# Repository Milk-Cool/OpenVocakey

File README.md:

# OpenVocakey
An open-source ESP32-based vocal synthesis keyboard

## What is this?
This is exactly what it sounds like -- a DIY open-source keyboard capable of producing human-like speech in the form of singing. Yes, just like VOCALOID -- except it is live, so it would be closer to [Pocket Miku](https://youtu.be/Uk6hSK1DDR4) or the [VOCALOID Keytar](https://en.wikipedia.org/wiki/Vocaloid_Keyboard).

### What is this based on?
It uses [espeak-ng](https://github.com/espeak-ng/espeak-ng) at its core, with the wrapper being [BackgroundAudio](https://github.com/earlephilhower/BackgroundAudio) and the wrapper wrapper being `tts.cpp`. This means that the voices are actually very customizable! You can use formant settings to adjust the voice to your liking and then upload it to the device.

## How do I use it?
You can buy a [Cardputer](https://shop.m5stack.com/products/m5stack-cardputer-adv-version-esp32-s3) if you wanna check the project out, or make a keyboard of your own with the provided gerber and KiCad files. Then, you can upload songs and files using the [online tool](https://milk-cool.github.io/OpenVocakey/) (works best with Chromium-based browsers).

### Song format
A song is just a text file containing Japanese characters (hiragana or katakana but NOT kanji), with each syllable on its own line, for example:
```
き
ら
き
ら
ひ
か
る
```

You can also add ending syllables after a base syllable, separated by a comma (will not be stretched):
```
こ,い
```

> Note: you can input more than one syllable on one line, but then the vowel stretch won't work properly.

### Voice format
This is just an espeak-ng voice, but without the `pitch` and `language` fields (those are added automatically). See [the documentation for espeak-ng](https://github.com/espeak-ng/espeak-ng/blob/master/docs/voices.md) for specific instructions on how to create a voice.

### Assembling the board
If you decided to make your own keyboard, first of all, you'd have to order a two-layer PCB. This is because one of the traces (yes, just one!) is on the other side of the PCB. Then, once it arrives, you have to solder MX-Cherry style keyboard switches into the holes on the bottom of the board (and add keycaps to your liking) and solder on female 2.54mm headers everywhere else. Then, you can insert a 30-pin ESP32-WROOM board into the double headers (with the USB port facing outwards), an i2c SSD1306 display into the middle headers (facing inwards) and a MAX98357a i2s audio amplifier into the remaining headers (facing outwards; don't forget to connect a speaker!!). Also don't forget to solder on the 10K resistors for pull-up below the ESP32. Then you can print out the case (`case/`), slide the board inside and screw it down on the sides with M6x20 bolts. Then you'd have to upload the firmware to the ESP32 and you're done!!

> Note: see `bom.csv` for the Bill of Materials.

### Navigating the menus
You can press BOOT/G0 on your board to enter the menu. From there, you can press the two leftmost white buttons to move left or right, and the rightmost two white buttons for cancelling and confirming your actions (e. g. entering a submenu and then confirming the volume change using the rightmost button). You can also press G0 again to leave the menu.

Go on, play around with the menus and see what you can customize!!

> Note: most settings are discarded upon reboot.

### Using the website

You can use the [online tool](https://milk-cool.github.io/OpenVocakey/) to manage the files on your OpenVocakey. First, click "Connect" in the corner and select your board. Then, you can download the already existing files by clicking on them, or upload new files by first selecting the file, then giving it a name and then clicking "upload".

> Note: that **WILL** overwrite the file! Be careful.

## Why does this exist?
I was always fascinated by vocaloids and the two aforementioned products in paticular, hence I decided to make this. Those can be hard to get and rather unaffordable, especially in non-first-world countries, therefore I think people might find this useful.

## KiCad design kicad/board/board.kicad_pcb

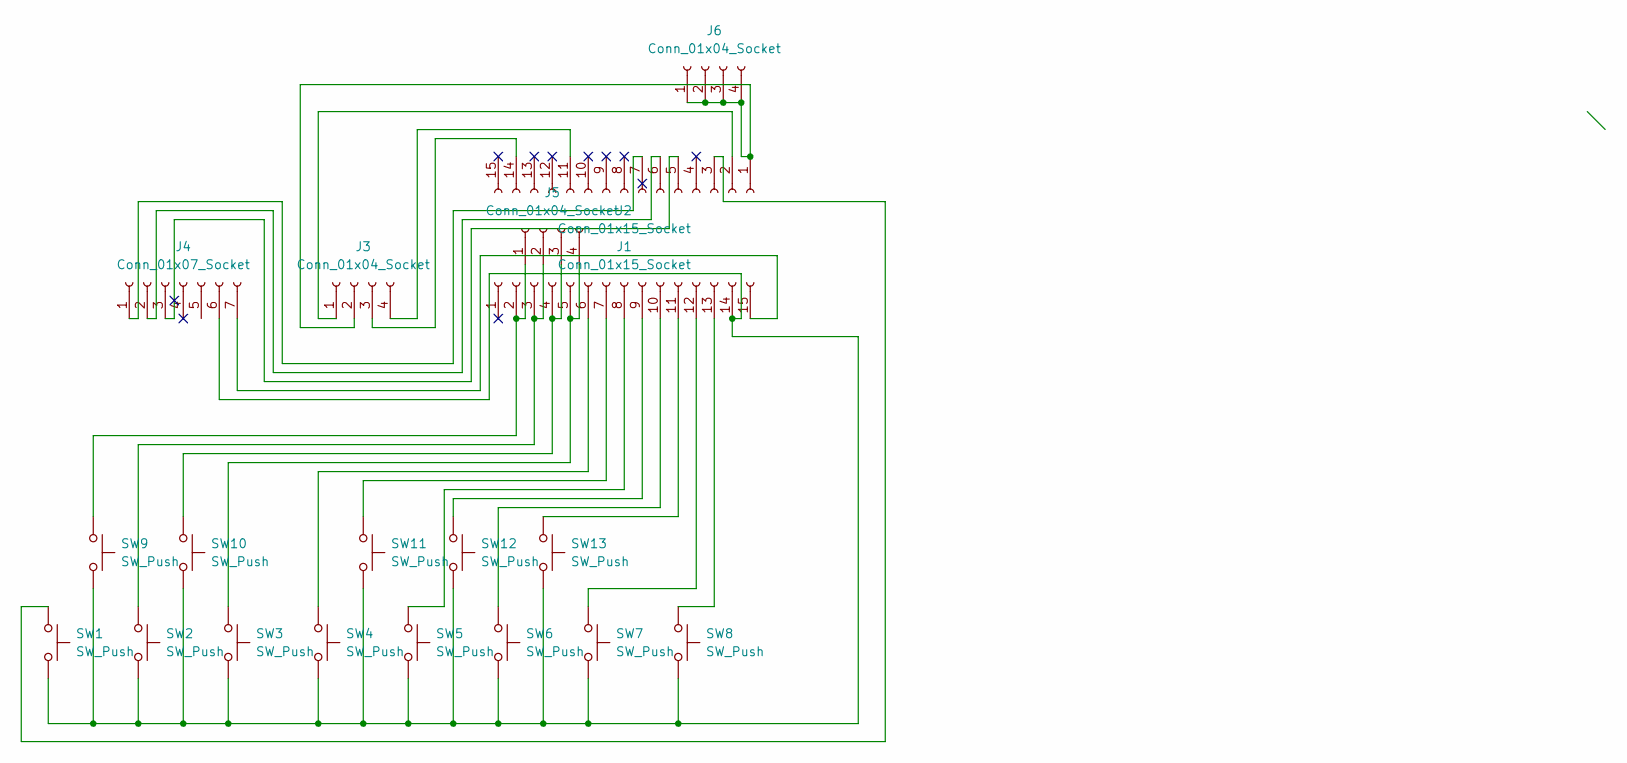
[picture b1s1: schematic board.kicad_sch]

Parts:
J1, J2: Conn_01x15_Socket; PinHeader_1x15_P2.54mm_Vertical
J3, J5, J6: Conn_01x04_Socket; PinHeader_1x04_P2.54mm_Vertical
J4: Conn_01x07_Socket; PinHeader_1x07_P2.54mm_Vertical
SW1, SW2, SW3, SW4, SW5, SW6, SW7, SW8, SW9, SW10, SW11, SW12, SW13: SW_Push; SW_Cherry_MX_1.00u_PCB

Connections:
unnamed: J1.2, J5.1, SW9.1
unnamed: J1.3, J5.2, SW2.1
unnamed: J1.4, J5.3, SW10.1
unnamed: J1.5, J5.4, SW3.1
unnamed: J1.6, SW4.1
unnamed: J1.7, SW11.1
unnamed: J1.8, SW5.1
unnamed: J1.9, SW12.1
unnamed: J1.10, SW6.1
unnamed: J1.11, SW13.1
unnamed: J1.12, SW7.1
unnamed: J1.13, SW8.1
unnamed: J1.14, J4.6, SW1.2, SW2.2, SW3.2, SW4.2, SW5.2, SW6.2, SW7.2, SW8.2, SW9.2, SW10.2, SW11.2, SW12.2, SW13.2
unnamed: J1.15, J4.7
unnamed: J2.1, J3.2, J6.1, J6.2, J6.3, J6.4
unnamed: J2.2, J3.1
unnamed: J2.3, SW1.1
unnamed: J2.5, J4.3
unnamed: J2.6, J4.2
unnamed: J2.7, J4.1
unnamed: J2.11, J3.4
unnamed: J2.14, J3.3

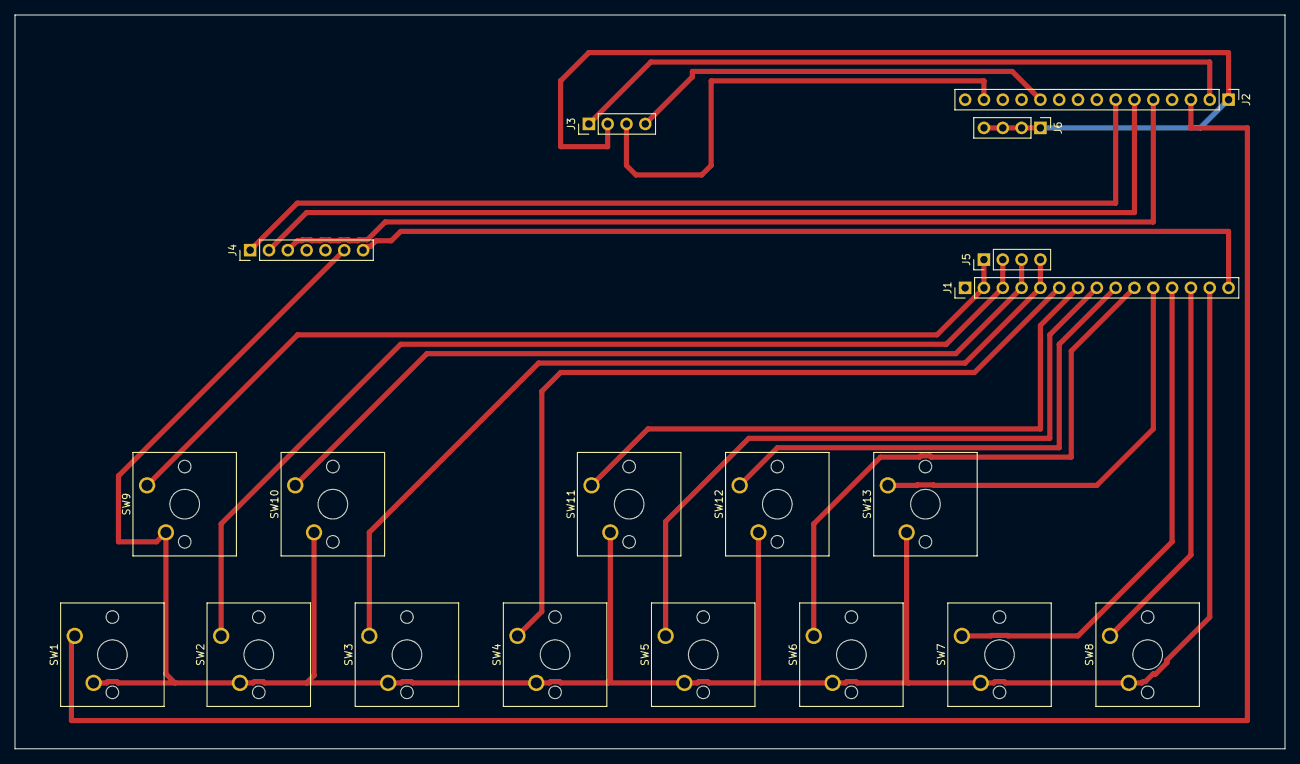
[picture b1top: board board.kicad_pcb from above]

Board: 2 copper layers, 171.4 x 99.1 mm, 19 parts (0 on the bottom side), 22 nets.

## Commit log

2026-04-30 YAAYA i figured out the pitch
2026-04-30 SOME SUCCESS!!!
2026-04-30 switch to japanese only
2026-04-30 twinkle twinkle little star played with the keyboard!!
2026-04-30 made it just a little faster
2026-05-01 a potential slight performance fix
2026-05-01 patch library to have a smaller audio buffer
2026-05-01 it's in tune now!
2026-05-01 added lyrics display
2026-05-01 songs and voicebanks storage
2026-05-01 prolong the vowels more
2026-05-02 reset button
2026-05-02 rewrite input stack
2026-05-02 add option to change wpm and vowel stretch
2026-05-02 add katakana support
2026-05-03 OOPS
2026-05-05 A LOT of fixes + custom board support
2026-05-05 config menu!! (only for custom board)
2026-05-05 trim paths in menu
2026-05-06 port new code to cardputer
2026-05-06 control panel
2026-05-06 update base case
2026-05-06 bugfix
2026-05-06 added a transpose function
2026-05-06 upload firmware files
2026-05-06 readme and pretty pictures
2026-05-06 add kicad project & gerber files
2026-05-06 add resistors to README
2026-05-06 Added BOM
2026-05-06 upload zine page & pcb pic
2026-05-09 update bom with headers
2026-05-10 add schematic to readme
2026-05-10 add zipped gerbers
2026-05-13 upload 3d model of the case & update zine and readme
2026-05-13 add .step file
2026-05-13 update readme's assembly instructions
2026-05-13 fix slow voice rendering on cardputer
2026-05-19 add support for ending syllables
